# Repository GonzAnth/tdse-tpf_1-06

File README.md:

<div align="center">

# UNIVERSIDAD DE BUENOS AIRES
**Facultad de Ingeniería** **TA134 - Taller de Sistemas Embebidos** Curso 1 - Grupo 6

## Sistema de Riego Automático 

**Autores:** Gonzalo Antahuara (109965) & Dante Mele Ientile (109494)  
**Fecha:** 06/03/2026  
**Cuatrimestre de cursada:** 1er cuatrimestre 2025

---

)

</div>

El presente trabajo consiste en la implementación de un **sistema de monitoreo y control de riego autónomo** basado en la placa de desarrollo **NUCLEO-F103RB**. 
El sistema mide variables ambientales tales como la temperatura y la humedad para gestionar la activación de una electroválvula, optimizando el uso del agua en cultivos de pequeña escala.

## Características Principales

* **Mediciones:** Uso del sensor digital **SHT85** para mediciones de temperatura (± 0,1 °C) y humedad (± 1,5 %RH).
* **Modos de Operación:** Selección mediante la interfaz de usuario entre los modos *Manual*, *Timer* (por tiempo fijo) y *Sensor & Timer* (automático por umbrales).
* **Interfaz de Usuario:** Navegación por menús en pantalla **LCD 20x4** con retroalimentación auditiva mediante un **buzzer**.
* **Almacenamiento de Datos:** Almacenamiento de los parámetros de la configuración del usuario (umbrales y tiempos) en la **memoria Flash interna** del microcontrolador.
* **Gestión de Energía:** Implementación de **Modo Sleep** para reducir el consumo eléctrico durante periodos de inactividad.

## Especificaciones Técnicas

### Hardware
* **Microcontrolador:** Placa NUCLEO-F103RB basada en **ARM Cortex-M3**.
* **Sensor:** Sensor SHT85 comunicado vía protocolo **I2C** con verificación **CRC-8**.
* **Actuador:** Módulo relé con **optoacoplador** para aislamiento eléctrico de la etapa de potencia.
* **Alimentación:** Fuente externa de 5 V / 1 A para garantizar la autonomía del sistema.
* **Diseño Físico:** PCB diseñada en formato **Shield** para robustez mecánica y reducción de ruido eléctrico.

### Firmware
* **Arquitectura:** Bare-metal con esquema de *Super-Loop* y tick de 1 ms.
* **Paradigma:** Sistema disparado por eventos *Event-Triggered System* utilizando Máquinas de Estados no bloqueantes.
* **Rendimiento:** Optimización del peor tiempo de ejecución **WCET**, logrando una ocupación máxima de CPU del 59,1 % en el peor de los casos.

## Estructura del Proyecto

* `task_system`: Máquina de estados principal que administra los modos de operación y lógica de riego.
* `task_menu`: Gestión del menú interactivo y actualización parcial de la pantalla LCD.
* `task_sht85`: Controlador del sensor de humedad y temperatura mediante interrupciones.
* `task_adc`: Monitoreo de la salud del sistema (tensión y temperatura interna) vía DMA.
* `task_actuator`: Control escalable del módulo relé y buzzer.

## Organización del Repositorio

El ciclo de desarrollo se gestiona aplicando estándares de control de versiones y revisión de Pull Requests:
* **main**: Rama de entregables. Contiene los archivos en PDF, la presentación y esta documentación.
* **develop**: Rama activa de desarrollo. Contiene el firmware completo del proyecto (/App, /Drivers, etc.).
* **hardware**: Desarrollo de hardware del proyecto.

## Documentación Adicional

* **[Memoria del Trabajo Final - Grupo 6](https://github.com/GonzAnth/tdse-tpf_1-06/blob/main/1_Memoria%20del%20Trabajo%20Final%20-%20Grupo%206.pdf)**.
* **[Presentación TDSE - Grupo 6](https://github.com/GonzAnth/tdse-tpf_1-06/blob/main/3_Presentaci%C3%B3n%20TDSE%20-%20Grupo%206.pdf)**.

## 👥 Autores
* **Gonzalo Antahuara**
* **Dante Mele Ientile**

---
*Este proyecto fue desarrollado como Trabajo Final para el Taller de Sistemas Embebidos de la Facultad de Ingeniería de la Universidad de Buenos Aires (FIUBA)*.

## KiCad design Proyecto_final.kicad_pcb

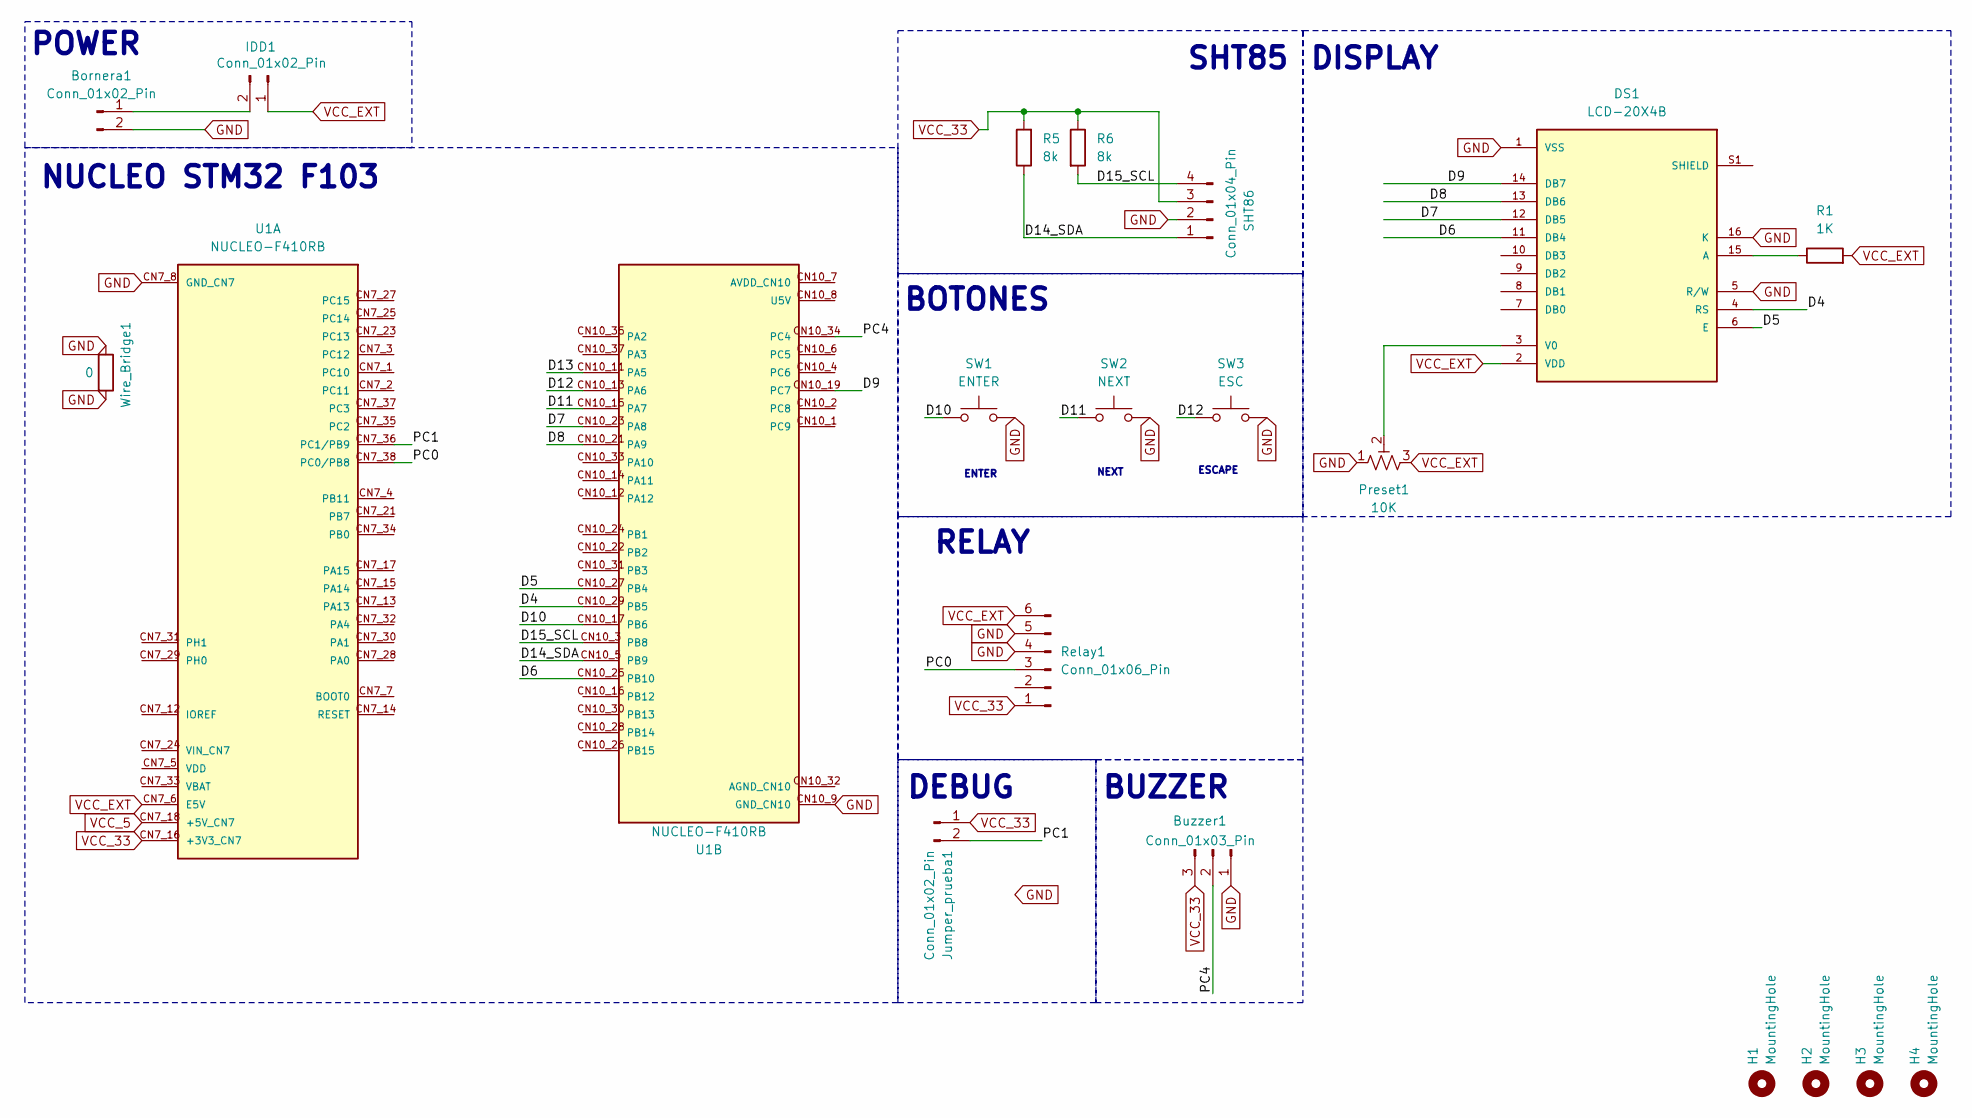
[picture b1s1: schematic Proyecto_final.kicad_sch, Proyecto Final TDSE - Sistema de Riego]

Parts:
Bornera1: Conn_01x02_Pin; TerminalBlock_MaiXu_MX126-5.0-02P_1x02_P5.00mm
Buzzer1: Conn_01x03_Pin; PinHeader_1x03_P2.54mm_Vertical
DS1: LCD-20X4B; LCD_LCD-20X4B; PARTREV N/A
H1, H2, H3, H4: MountingHole; MountingHole_3.2mm_M3
IDD1: Conn_01x02_Pin; PinHeader_1x02_P2.54mm_Vertical
Jumper_prueba1: Conn_01x02_Pin; PinHeader_1x02_P2.54mm_Vertical
Preset1: 10K; Potentiometer_Bourns_3296W_Vertical
R1: 1K; R_Axial_DIN0309_L9.0mm_D3.2mm_P20.32mm_Horizontal
R5, R6: 8k; R_Axial_DIN0309_L9.0mm_D3.2mm_P12.70mm_Horizontal
Relay1: Conn_01x06_Pin; PinHeader_1x06_P2.54mm_Vertical
SHT86: Conn_01x04_Pin; PinHeader_1x04_P2.54mm_Horizontal
SW1: ENTER; SW_PUSH_6mm_H5mm
SW2: NEXT; SW_PUSH_6mm_H5mm
SW3: ESC; SW_PUSH_6mm_H5mm
U1: NUCLEO-F410RB; ST_NUCLEO-F410RB; PARTREV 13
Wire_Bridge1: 0; R_Axial_DIN0309_L9.0mm_D3.2mm_P12.70mm_Horizontal

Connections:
/D4: DS1.4 (RS), U1.CN10_29 (PB5)
/D5: DS1.6 (E), U1.CN10_27 (PB4)
/D6: DS1.11 (DB4), U1.CN10_25 (PB10)
/D7: DS1.12 (DB5), U1.CN10_23 (PA8)
/D8: DS1.13 (DB6), U1.CN10_21 (PA9)
/D9: DS1.14 (DB7), U1.CN10_19 (PC7)
/D10: SW1.1, U1.CN10_17 (PB6)
/D11: SW2.1, U1.CN10_15 (PA7)
/D12: SW3.1, U1.CN10_13 (PA6)
/D13: U1.CN10_11 (PA5)
/D14_SDA: R5.1, SHT86.1, U1.CN10_5 (PB9)
/D15_SCL: R6.2, SHT86.4, U1.CN10_3 (PB8)
/PC0: Relay1.3, U1.CN7_38 (PC0/PB8)
/PC1: Jumper_prueba1.2, U1.CN7_36 (PC1/PB9)
/PC4: Buzzer1.2, U1.CN10_34 (PC4)
GND: Bornera1.2, Buzzer1.1, DS1.1 (VSS), DS1.5 (R/W), DS1.16 (K), Preset1.1, Relay1.4, Relay1.5, SHT86.2, SW1.2, SW2.2, SW3.2, U1.CN7_8 (GND_CN7), U1.CN7_19 (GND_CN7), U1.CN7_20 (GND_CN7), U1.CN7_22 (GND_CN7), U1.CN10_9 (GND_CN10), U1.CN10_20 (GND_CN10), Wire_Bridge1.1, Wire_Bridge1.2
unnamed: Bornera1.1, IDD1.2
unnamed: DS1.15 (A), R1.1
unnamed: DS1.3 (V0), Preset1.2
VCC_5: U1.CN7_18 (+5V_CN7)
VCC_33: Buzzer1.3, Jumper_prueba1.1, R5.2, R6.1, Relay1.1, SHT86.3, U1.CN7_16 (+3V3_CN7)
VCC_EXT: DS1.2 (VDD), IDD1.1, Preset1.3, R1.2, Relay1.6, U1.CN7_6 (E5V)

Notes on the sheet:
ENTER
BUZZER
ESCAPE
NUCLEO STM32 F103
RELAY
SHT85
NEXT
DEBUG
DISPLAY
POWER
BOTONES

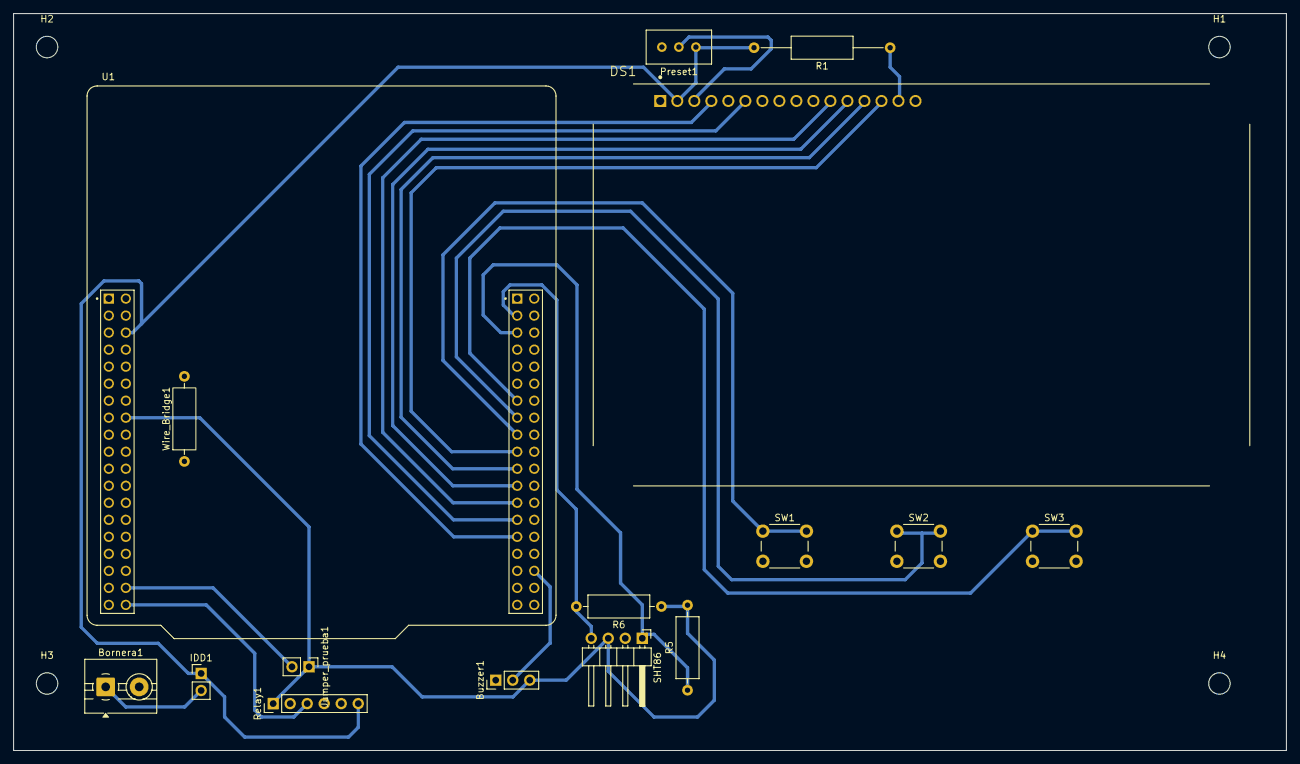
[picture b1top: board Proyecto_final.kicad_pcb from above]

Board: 2 copper layers, 190.0 x 110.0 mm, 20 parts (0 on the bottom side), 20 nets.

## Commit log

2025-06-12 Revisar codigo error
2025-06-22 Maquina de estados Menu
2025-07-02 upload plantillas
2025-12-28 fix statechar menu & primeras impresiones LCD
2026-01-02 fix estados y nueva función de impresión
2026-01-02 nueva función display & refresh_screen
2026-01-03 fix en display & mem maquina de estados
2026-01-09 test copia tp3-06
2026-01-09 fix config file
2026-01-09 Debug config
2026-01-09 fix git ignore
2026-01-09 add sht85 lib
2026-01-09 Agregado I2C y debug config
2026-01-12 Implementacion ME menu
2026-01-13 Implementacion ME sensor con 3 botones
2026-01-14 ME Sht85 terminada
2026-01-14 Correcion includes
2026-01-16 ME System andando
2026-01-17 Integracion systema-sensor terminado
2026-01-18 Integracion menu
2026-01-18 add menu_interface.c
2026-01-18 Integracion menu-system-sensor, funcionando ok
2026-01-24 config básica adc
2026-01-24 ADC funcionando
2026-01-26 Nuevas funcione ADC
2026-01-26 maquina de estados implementada
2026-01-26 calculos & st_falla
2026-01-26 Test/adc (#2)
    * Configuración básica del ADC
    * Implementación de función de cambio de canales
    * Lectura de sensores internos (Temp & Bat)
    * Cálculo de valores medidos
    --------
2026-01-27 Primer implmentacion maquina de estados
2026-01-27 FIX bug riego
2026-01-28 agregado logica de eventos de baja prioridad
2026-01-28 encabezados adc
2026-01-28 Integracion/system-sensor-menu-adc (#3)
    Primera integración funcional del trabajo, incluye:
    * Máquina de estado del sensor SHT85 y botones
    * Máquina de estados del Menú
    * Impresiones básicas en display
    * Máquina de estados ADC
    * Máquina de estados del system
2026-01-28 update encabezados
2026-01-28 Fix eventos baja prioridad
2026-01-28 Fix/Eventos baja prioridad System (#4)
    * Update encabezados
    * Reemplazo de función "put_mode" por eventos de baja prioridad
    * Ahora existe un tipo de dato "task_system_mode_t" para seleccionar los modos del systema
    ---------
2026-01-28 Encabezados sht85 & menu
2026-01-28 WCET config
2026-01-28 primera versión de print por etapas
2026-01-29 Implementacion ME actuator
2026-01-29 Implementacion ME actuator (#5)
2026-01-29 Primera version funcional
2026-01-30 optimización escritura y modo sensor&timer
2026-01-30 Create memoria flash
2026-01-30 Agregado de estados de configuracion
2026-01-30 orden de modo config
2026-01-30 getters en systema
2026-01-30 agregado de modo manual explicito
2026-01-30 Feature/system manual mode & functions (#6)
    * Se agregan funciones getters y setters para el systema
    * Se agrega el modo manual explicito
2026-01-30 Manejo de modo manual en menu
2026-01-30 hotfix: check null en puntero
2026-01-30 actualizamos estructura y variables del systema
2026-01-30 hotfix: tipos de datos & compilador
2026-01-30 Squashed commit of the following:
    commit 8982695b0c1b42f1878dad498643f6389d7d25ac
    Author: Dante Mele Ientile <dantemeleientile@gmail.com>
    Date: Fri Jan 30 13:13:09 2026 -0300
    hotfix: tipos de datos & compilador
2026-01-30 impresion de variables
2026-01-30 Feature/menu-display (#7)
    Implementación del menu y comportamiento del display
    Detalles:
    * Impresión por etapas
    * Implementación de cursor
    * Get & set valores del system
2026-01-30 system indica la falla y reporta ok a adc
2026-01-30 falla funcionando
2026-01-30 Feature/reporte falla system menu (#8)
    Mejoras:
    * El systema reporta las fallas al menu y al adc (fix)
    * Nuevo estado en el menu para mostar la falla en pantalla
    * Se deja la posibilidad de agregar otros put_event_task_XXX() desde el systema para casos de falla.
2026-01-30 primera versión de impresion estado bomba
2026-01-30 reporte bomba funcionando
2026-01-30 Funcionalidad ok
2026-01-30 Feature/config and reporte riego (#9)
2026-01-30 Squashed commit of the following:
    commit d967b297e99b3761281ca08a33618bf58a1d99d6
    Author: Dante Mele Ientile <dantemeleientile@gmail.com>
    Date: Fri Jan 30 18:16:34 2026 -0300
    Feature/config and reporte riego (#9)
    commit a7da3367b9f14a6e2196e48f8851d17a716a806b
    Author: Dante Mele Ientile <dantemeleientile@gmail.com>
2026-01-31 Quitamos modo de la flash
2026-01-31 Actualización del menu para aceptar cambios en flash
2026-01-31 fix display
2026-01-31 Feature/memoria flash (#10)
    Driver memoria flash
    Modificación del menu para evitar escribir la memoria seguido
    ---------
2026-02-01 Fix funcion put_event_task_xx
    Fix:
    - He arreglado los eventos que le pasamos a la funcion put_event_task_xx en cada maquina de estados
    - Elimine los estados extras de quedaron de las primeras pruebas con botones
2026-02-01 nueva función para imprimir en 4 partes
2026-02-01 1er version con interrupciones
2026-02-01 activo event_IT desde .ioc & ajustes finales
2026-02-01 fix event & clean lib sht85
2026-02-01 Feature/optimizar wcet sht85 (#11)
    Modificar lib SHT85 para mejorar su performance
    Antes = 211 -> Ahora = 32
    Driver SHT85 por interrupciones
    Modificación en la máquina de estados task_sht85.c
    Update .ioc para permitir IT en I2C
    Limpieza de estados y eventos viejos
2026-02-01 1ere versión funcional
2026-02-01 Squashed commit of the following:
    commit df4b1f8f6bc53b3c194e909a01cca904509cbd8d
    Author: Dante Mele Ientile <dantemeleientile@gmail.com>
    Date: Sun Feb 1 04:02:49 2026 -0300
    Feature/optimizar wcet sht85 (#11)
    Modificar lib SHT85 para mejorar su performance
    Antes = 211 -> Ahora = 32
2026-02-01 Impresión de a 4 partes funcionando
2026-02-01 Manejo de umbrales y adc_req
2026-02-01 fix bug 3 cifras
2026-02-01 fix umbral temp
2026-02-02 Fix/optimizar wcet menu display (#13)
    Optimización del WCET de task_menu
    Antes = 672, Ahora = 570
    Implementación y uso de función para imprimir por partes
    Ajustes en impresiones por pantalla y umbrales
2026-02-02 Squashed commit of the following:
    commit 53f3b2f602549822e8d75c72daed34b7e8e49aab
    Author: Dante Mele Ientile <dantemeleientile@gmail.com>
    Date: Mon Feb 2 19:22:54 2026 -0300
    Fix/optimizar wcet menu display (#13)
    Optimización del WCET de task_menu
    Antes = 672, Ahora = 570
2026-02-02 feature/adc-whit-DMA (#12)
    Dejamos de usar IT y usamos DMA
    Antes = 154 -> Ahora = 25
    Configuramos DMA en .ioc
    Se reduce la máquina de estados
    Nota: Cambios transparentes para system
    commit 53f3b2f602549822e8d75c72daed34b7e8e49aab
2026-02-02 Squashed commit of the following:
    commit 4760cfef714e1bd77ed94f0fe5a3703bfeba240a
    Author: Dante Mele Ientile <dantemeleientile@gmail.com>
    Date: Mon Feb 2 19:55:39 2026 -0300
    feature/adc-whit-DMA (#12)
    Dejamos de usar IT y usamos DMA
    Antes = 154 -> Ahora = 25
2026-02-02 Fix Nombres
2026-02-02 Fix/configuracion put event task xx (#14)
    Se modifica la forma de ingresar eventos a otras tareas:
    Antes:
    put_event_task_system(p_task_adc_cfg->ev_sys_adc_ok);
    Ahora:
    put_event_task_system(EV_SYS_ADC_OK);
    ---------
2026-02-03 HOTFIX: sintaxis estructura
2026-02-03 fix guardado memoria flash
2026-02-03 tiempos reales funiconando
2026-02-03 conversion de tiempo y update periodico de display
2026-02-03 ajustes prints
2026-02-05 fix texto "bomba"
2026-02-05 Modo sleep comentado
2026-02-06 sleep funcionando
2026-02-06 Feature/sleep mode & sytem time (#15)
    Configuración de tiempos en minutos
    Fixes en texto del display
    Funcionalidad Pin DEBUG: Pasar minutos a segundos para debugear
    Implementación Sleep mode
2026-02-06 configuración para relay
2026-02-06 primera versión con buzzer + fix FALLA sht85
2026-02-06 casos de falla en sht85 funcionando
2026-02-06 beep cada vez que se toca un botón
2026-02-06 Feature/relay and buzzer (#16)
    Funcionalidades y correcciones:
    Agregado de pines para relay y buzzer
    Corrección bug I2C error en SHT85 (ErrorCallback & Timeout)
    UX: Beep cada vez que se toca un botón
    * configuración para relay
    * primera versión con buzzer + fix FALLA sht85
2026-02-13 cambio pines para soldar a pcb
2026-02-13 PCB Pins (#17)
    Se cambian pines para soldar a pcb
    - PC0 -> Relay
    - PC1 -> Debug
    - PC4 -> Buzzer
2026-02-17 Squashed commit of the following:
    commit ea7c2754c499778f2a0bbfaadfffe48648c45035
    Author: Dante Mele Ientile <dantemeleientile@gmail.com>
    Date: Fri Feb 13 03:26:44 2026 -0300
    PCB Pins (#17)
    Se cambian pines para soldar a pcb
    - PC0 -> Relay
2026-02-17 fix encabezados
2026-02-17 Fix texto display
2026-02-17 Fix/encabezados (#18)
    Se actualiza la descripción de todos los encabezados
2026-02-20 Primera modificación logger
2026-02-20 quitamos optimización de compilador, modo release funcionando
2026-02-20 Fix volatile por prolijidad
2026-02-20 Feature/release compilation (#19)
    Se modifica código y la configuración del compilador:
    Si se compila en modo Release el monitor no se inicializa
    El monitor sigue disponible al compilar en modo Debug
    Por ser un prototipo, eliminamos la optimización del compilador en modo release quedó en None (-O0)
    Agregamos .bin como output
2026-02-20 Lote 1 revisado
2026-02-20 lote 2 competado
2026-02-20 Lote 4 finalizado
2026-02-20 ultimo lote
2026-02-20 Modificación de "sensor" x "button"
2026-02-20 compilación
2026-02-21 Chore/code cleanup (#20)
    Limpieza de dead-code y comentarios
    Algunos detalles:
    Refactor: Cambio de nombre "task_sensor" por "task_button"
    Se eliminan comentarios heredados de TPs
    Actualización de debug printouts
2026-03-02 Versión v1.0.0
2026-03-06 HOTFIX: update time task_sht85
2026-03-06 update archivos
2026-03-06 names & logo fiuba
2026-03-06 Create README.md
    Readme completo
2026-03-06 Add links
2026-03-06 Update files & readme
